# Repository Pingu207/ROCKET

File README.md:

# ROCKET (TVC)

A rocket using thrust vector control (TVC), with an onboard ESP32-WROOM-32 flight computer and sensors on a custom PCB.

## Overview
This project combines a gimbaled thrust-vectoring motor mount with a custom flight computer 
to actively stabilize the rocket during ascent. Progress is being logged as part of Hack 
Club's Stardance challenge.

## Hardware
- **MCU:** ESP32-WROOM-32
- **Barometer:** BMP280 (wired via I2C)
- **Servos:** 2x 20 kg·cm servos for TVC gimbal actuation
- **Power:** 2S LiPo battery for servo supply
- **Pyro channels:** Parachute ejection circuit (schematic complete)
- **PCB:** Custom board housing flight computer + sensors (schematic in progress)

## Mechanical
- TVC mount fully built, with weight-reduction holes machined in
- First servo mount CAD'd and finished
- Rocket body and nosecone modeled in CAD and assembled with the TVC assembly

## Flight Simulation
Simulated the rocket's altitude, velocity, and acceleration profile:
- Fit a polynomial thrust curve using regression (Desmos)
- Derived an ODE (Riccati equation) factoring in gravity and drag
- Solved numerically in Python (matplotlib) for performance
- **Result:** predicted apogee of 268.65 m at 7.66 seconds

## Project Status
- [x] TVC mount designed, built, and weight-optimized
- [x] Servo mount CAD finished
- [x] Body + nosecone CAD assembled with TVC
- [x] BMP280 wired (I2C)
- [x] Pyro firing (parachute ejection) circuit designed
- [x] Flight simulation (altitude/velocity/acceleration, apogee prediction)
- [x] Servo wiring for TVC actuation
- [x] GPS integration into schematic
- [x] Finish full PCB schematic
- [ ] PCB fabrication
- [ ] Static fire / ground testing  
- [ ] First test flight

## Devlog
Full build log with photos and hours logged: 
[Stardance project page](https://stardance.hackclub.com/projects/45265)

(The mount inside the rocket to hold the PCB on impact)

(An exploded CAD design of all the components inside the rocket)

(A fully CADded TVC mount with the mounting holes)

(The Front side of the 3d PCB CAD)

(This is the 2D model of the PCB with all of the components)

(This is the schematic of the PCB with everything routed)

(This is an image of the inside of the rocket and how its layout is)

(This is a photo of the rocket from the bottom)

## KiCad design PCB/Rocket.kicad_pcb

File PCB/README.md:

# Rocket Flight Computer

A custom flight computer for a TVC model rocket that steers the rocket during boost and deploys its parachutes on the way down.

## What it does
- **Steers the rocket** with thrust vector control: two servos gimbal the motor to keep the rocket flying straight.
- **Deploys recovery** with two pyro channels: a drogue chute at apogee and the main chute at a set altitude.
- **Logs the flight** (acceleration, rotation, altitude, servo positions, battery voltages) to a microSD card.

## How it works
An ESP32 reads an ICM-42688 IMU and a BMP280 barometer. It detects launch, tracks the rocket's orientation and drives the servos to correct any tilt. When the barometer shows the rocket has stopped climbing, it fires the drogue; the main fires lower on the way down. Each pyro channel is optoisolated by an optocoupler to protect the ESP32 and has continuity sensing, so the board confirms the e-matches are connected before launch.

The logic, servos and pyros each run from their own battery, so a servo stall or a pyro firing can't brown out the computer. The board is programmed over USB-C

## Computer Module Subsystem

Contains the ESP32 as the 'brain' of the board, contains decoupling/bulk capacitors for the ESP power pins, RC decoupling for sensing pins, 2 SPI and an I2C communication circuit, 2 switches for RESET/BOOT on the ESP, various other resistors for signal lines and pull up on I2C/SPI lines, and a buzzer for detection of the apparatus after landing.

## USB Input and Conversion(USB-UART) Subsystem

Uses a 14 pin USB-C Receptacle for programming of the ESP32 over USB(Note: On the PCB, only one side of the receptacle footprint is routed correctly due to space constraints, so it will only work when the cable is plugged in one specific way, not both). Contains a USBLC6-2SC6 transient voltage suppression diode array for ESD/Surge protection. The USB-UART conversion is handled by the CH340K, an auto reset transistor circuit is also in place to make the ESP32 enter boot mode when data is transferred. The VBUS from the USB can also power logic on the chip by feeding into the logic power buck converter(ORing with the battery), the line also contains a Schottky diode for protection.

## Barometer(BMP280) Subsystem

Uses the BMP280 as the barometer, contains 2 decoupling caps for the power pins and a pull up resistor for the SCL line. Wired for I2C communication with the ESP32. Since SDO is tied to GND and CSB is pulled high to +3V3, the BMP280 will be set to the I2C adress 0x76.

## Logic Power and GND subsystem

Uses a generic connector symbol(JST PH 2.0 connector is used on the PCB). Contains reverse protection and voltage testing(facilitated by ESP ADC pin(Sensor_VN or pin 5)) before the buck converter. The buck converter input is OR'd between the battery and the USBC VBUS input, so either can power the chip. The buck converter used is the AP63203WU, a 2A synchronous step-down (buck) DC-DC switching voltage regulator, which is used here to step down the voltage of the battery(2S LiPO, 7.4V nominal) to a usable 3.3V for the ESP32. It is fitted with its correct passives(Input and Output capacitors, inductors, and bootstrap capacitor) as specified by its datasheet(Note: No feedback resistors are required here because the chip outputs a fixed 3.3V due to its internal feedback loop). The output of the chip supplies power for all logic functions on the chip.

## SD Card Logging Subsystem

Uses an SD card slot for flight data logging. Wired SPI from the ESP32. Contains pullup resistors and proper decoupling/bulk caps.

## Servo Power Subsystem

Uses generic pin connectors here on the schematic and JST PH 2.0 on the PCB again. Uses an IRF7404 transistor for reverse protection. Power feeds into 2 TPS563200s, 3A step down voltage regulators. They have proper passives(Input and Output capacitors, inductors, bootstrap capacitor, and feedback resistor). They also have LEDs alongside each for indication. Power feeds into 2x3 pin headers where the servos will feed from, each power line contains a 470uF bulk cap. Each servo is also controlled via PWM from the ESP32.

## Pyro Firing Subsystem

Uses a generic connector symbol (JST PH 2.0 on the PCB). An SS34 Schottky diode provides reverse protection, and an LED shows when the pyro battery is connected. The battery voltage is measured by the ESP32. There are two firing channel(Drogue/Main). Each is driven by an ESP32 GPIO through a PC817 optocoupler. The optocoupler switches the gate of an IRLZ44N, with a 10k pulldown. The MOSFET switches the low side of the e-match, which connects to the board through 2-pin screw terminals. Each e-match has a flyback diode across it for protection. Each channel also has continuity sensing via an ESP32 ADC pin. The pyro ground is connected to the main GND through a 0Ω resistor. (Note: The continuity and voltage sensing need the grounds tied together. Also, the main channel uses an ESP strapping pin(IO5) so the pyro battery should only be connected once the board is powered on and on the pad.)
## Why I made it
I decided to design a PCB for this project in order to get experience with designing a more complex PCB with multiple subsystems, learn about embedded control, and fly a rocket without having to buy a COTS flight computer, because thats really cool you know?!!

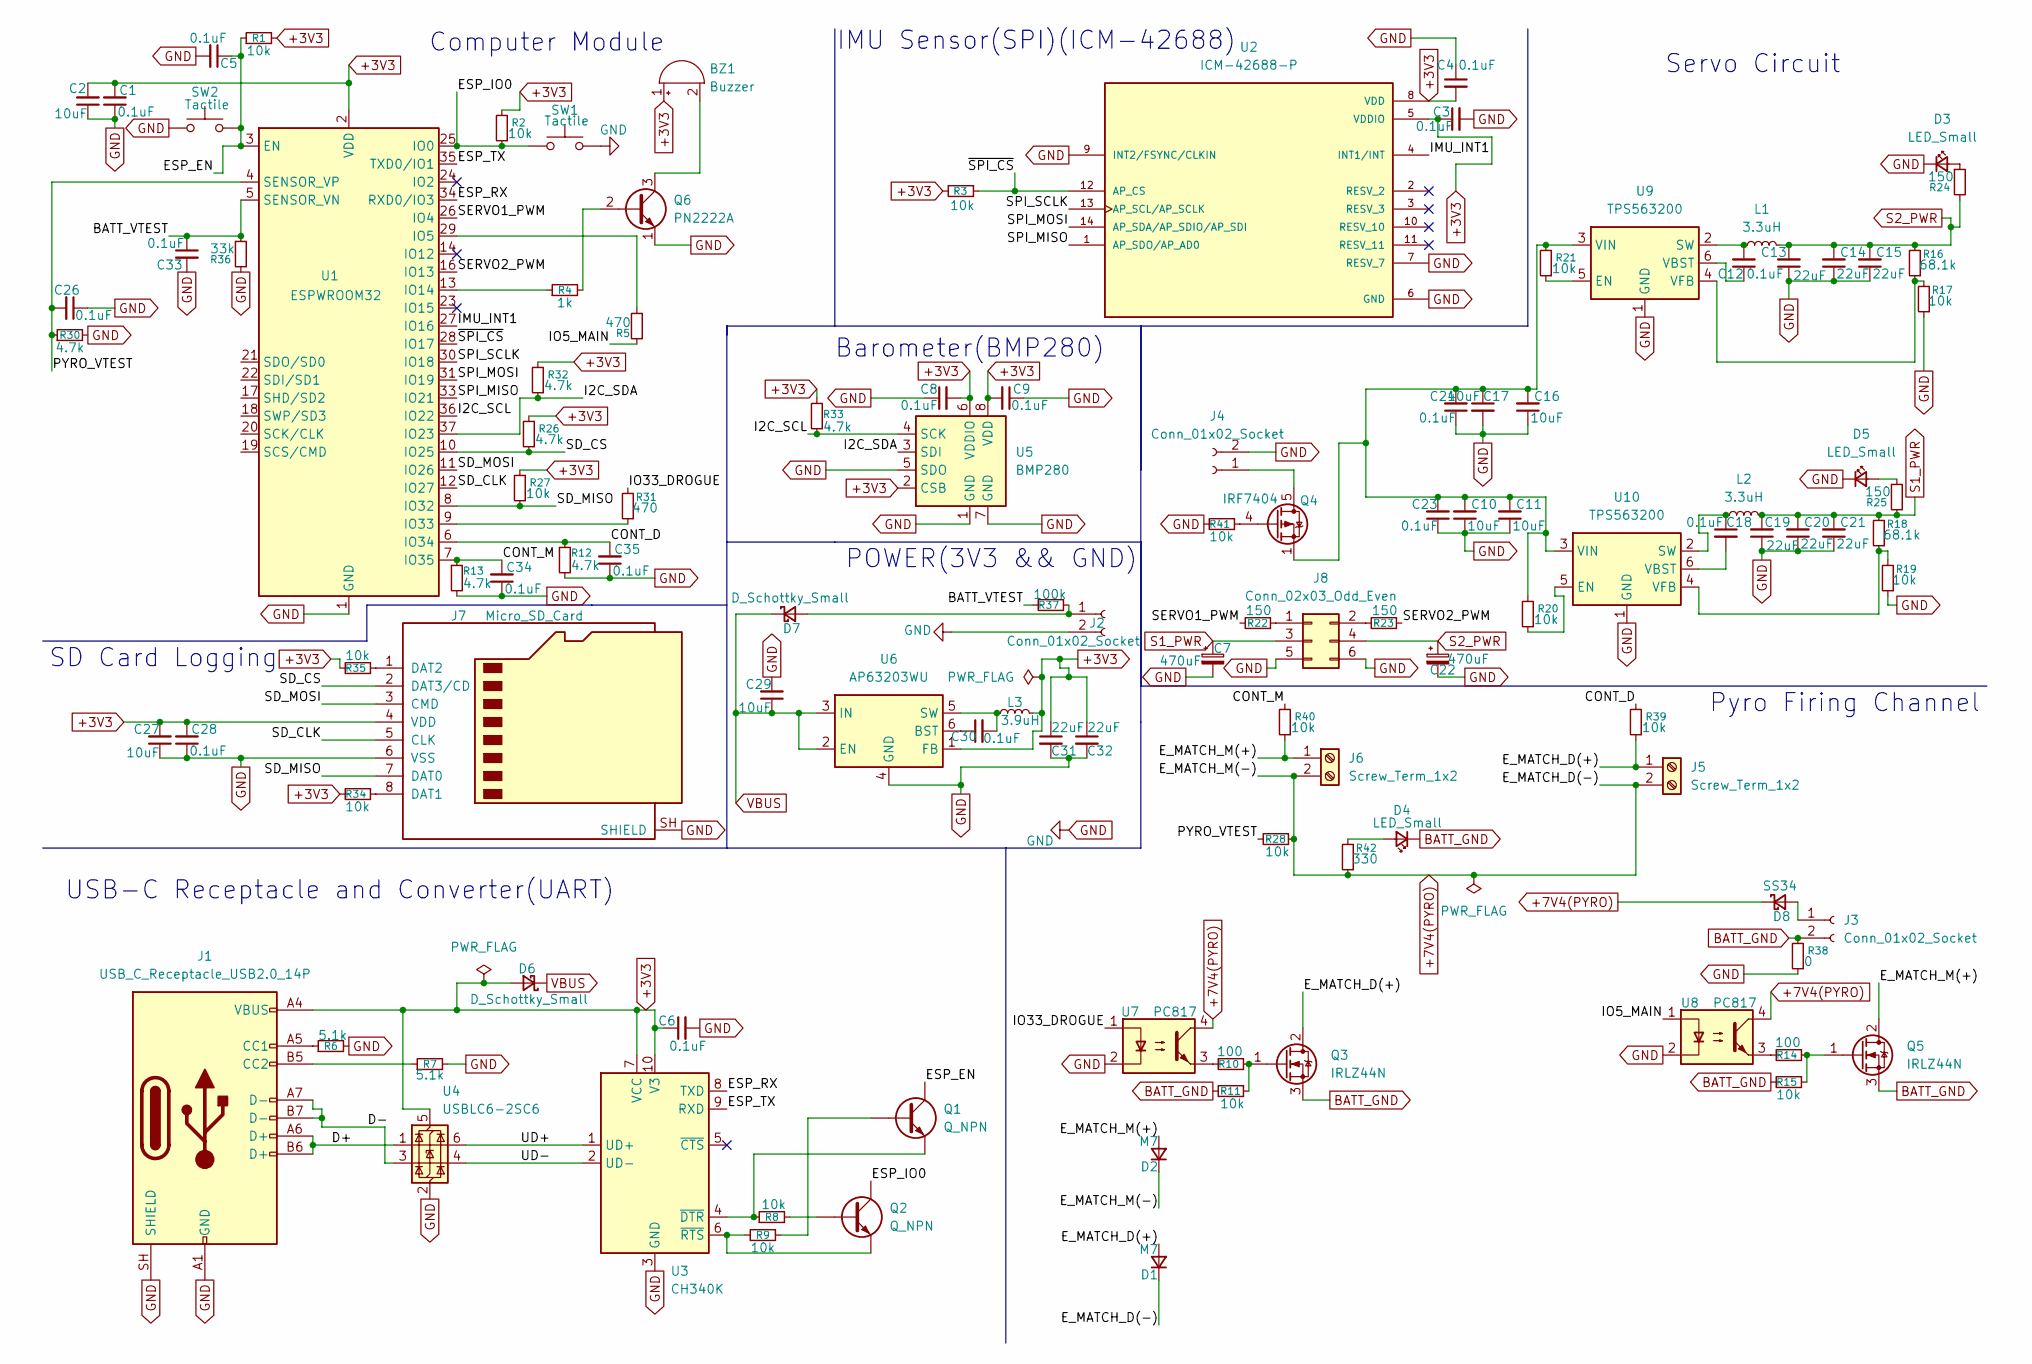
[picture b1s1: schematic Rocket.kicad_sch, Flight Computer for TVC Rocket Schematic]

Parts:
BZ1: Buzzer; BUZ-TH_BD9.0-P4.00-D0.6-FD; LCSC C96256
C1, C3, C4, C5, C6, C8, C9, C12, C18, C23, C24, C26, C28, C30, C33, C34, C35: 0.1uF; C0603; LCSC C125205
C2, C10, C11, C16, C17, C27, C29: 10uF; C0805; LCSC C440198
C7, C22: 470uF; CAP-SMD_BD10.0-L10.3-W10.3-FD; LCSC C976030
C13, C14, C15, C19, C20, C21, C31, C32: 22uF; C0805; LCSC C86816
D1, D2: M7; SMA_L4.3-W2.6-LS5.2-RD; LCSC C95872
D3, D4, D5: LED_Small; LED0603-FD; LCSC C19171390
D6, D7: D_Schottky_Small; SMC_L6.9-W5.9-LS7.9-RD; LCSC C154551
D8: SS34; SMC_L6.9-W5.9-LS7.9-RD; LCSC C154551
J1: USB_C_Receptacle_USB2.0_14P; USB-C-TH_KH-TYPE-C-CY-14P; LCSC C2919655
J2, J3, J4: Conn_01x02_Socket; CONN-TH_2P-P2.00_HC-PH-2A-M; LCSC C5359599
J5, J6: Screw_Term_1x2; CONN-TH_XY126V-5.0-2P; LCSC C557646
J7: Micro_SD_Card; TF-SMD_TF-115; LCSC C266620
J8: Conn_02x03_Odd_Even; HDR-TH_6P-P2.54-V-R2-C3-S2.54_A2541WV-2X3P; LCSC C5116479
L1, L2: 3.3uH; IND-SMD_L4.4-W4.2-A; LCSC C167207
L3: 3.9uH; IND-SMD_L5.0-W5.0; LCSC C42428060
Q1, Q2: Q_NPN; SOT-23-3_L3.0-W1.7-P0.95-LS2.9-BR; LCSC C2146
Q3, Q5: IRLZ44N; TO-220-3_L10.0-W4.5-P2.54-T; LCSC C38774
Q4: IRF7404; SOIC-8_L4.9-W3.9-P1.27-LS6.0-BL; LCSC C2997
Q6: PN2222A; TO-92-3_L4.9-W3.7-P1.27-L; LCSC C118536
R1, R2, R3, R8, R9, R11, R15, R17, R19, R20, R21, R27, R28, R34, R35, R39, R40, R41: 10k; R0603; LCSC C98220
R4: 1k; R0603; LCSC C22548
R5, R31: 470; R0603; LCSC C23179
R6, R7: 5.1k; R0603; LCSC C2907044
R10, R14: 100; R0603; LCSC C22775
R12, R13, R26, R30, R32, R33: 4.7k; R0603; LCSC C99782
R16, R18: 68.1k; R0603; LCSC C25976
R22, R23, R24, R25: 150; R0603; LCSC C2906994
R36: 33k; R0603; LCSC C2907028
R37: 100k; R0603; LCSC C14675
R38: 0; R0603; LCSC C95177
R42: 330; R0603; LCSC C105881
SW1, SW2: Tactile; SW-SMD_L3.9-W3.0-P4.45; LCSC C720477
U1: ESPWROOM32; WIFIM-SMD_ESP32-WROOM-32-N4; LCSC C82899
U2: ICM-42688-P; LGA-14_L3.0-W2.5-P0.50-TL; PARTREV 1.2; LCSC C1850418
U3: CH340K; ESOP-10_L4.9-W3.9-P1.00-LS6.2-BL-EP; LCSC C968586
U4: USBLC6-2SC6; SOT-23-6_L2.9-W1.6-P0.95-LS2.8-BL; LCSC C7519
U5: BMP280; LGA-8_L2.5-W2.0-P0.65_AMP6127; LCSC C83291
U6: AP63203WU; TSOT-26_L2.9-W1.6-P0.95-LS2.8-BL; LCSC C780769
U7, U8: PC817; DIP-4_L6.4-W4.6-P2.54-LS7.6-BL; LCSC C5350
U9, U10: TPS563200; TSOT-26_L2.9-W1.6-P0.95-LS2.8-BL; LCSC C97253

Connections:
+3V3: BZ1.1 (+), C1.2, C2.2, C3.1, C4.2, C6.1, C8.2, C9.2, C27.2, C28.2, C31.1, C32.1, D6.2 (A), J1.A4 (VBUS), J1.A9 (VBUS), J1.B4 (VBUS), J1.B9 (VBUS), J7.4 (VDD), L3.2, R1.2, R2.2, R3.2, R26.2, R27.2, R32.2, R33.2, R34.2, R35.2, U1.2 (VDD), U2.5 (VDDIO), U2.8 (VDD), U3.7 (VCC), U3.10 (V3), U4.5 (VBUS), U5.2 (CSB), U5.6 (VDDIO), U5.8 (VDD), U6.1 (FB)
+7V4(PYRO): D1.1 (K), D2.1 (K), D8.1 (K), J5.2, J6.2, R28.1, R42.1, U7.4, U8.4
/BATT_VTEST: C33.1, R36.1, R37.2, U1.5 (SENSOR_VN)
/CONT_D: C35.2, R12.1, R39.2, U1.6 (IO34)
/CONT_M: C34.2, R13.1, R40.2, U1.7 (IO35)
/D+: J1.A6 (D+), J1.B6 (D+), U4.1 (I/O1)
/D-: J1.A7 (D-), J1.B7 (D-), U4.3 (I/O2)
/ESP_EN: C5.1, Q1.3, R1.1, SW2.2, U1.3 (EN)
/ESP_IO0: Q2.3, R2.1, SW1.1, U1.25 (IO0)
/ESP_RX: U1.34 (RXD0/IO3), U3.8 (TXD)
/ESP_TX: U1.35 (TXD0/IO1), U3.9 (RXD)
/E_MATCH_D(+): D1.2 (A), J5.1, Q3.2 (D), R39.1
/E_MATCH_M(+): D2.2 (A), J6.1, Q5.2 (D), R40.1
/I2C_SCL: R33.1, U1.36 (IO22), U5.4 (SCK)
/I2C_SDA: R32.1, U1.37 (IO23), U5.3 (SDI)
/IMU_INT1: U1.27 (IO16), U2.4 (INT1/INT)
/IO5_MAIN: R5.1, U8.1
/IO33_DROGUE: R31.2, U7.1
/PYRO_VTEST: C26.2, R28.2, R30.1, U1.4 (SENSOR_VP)
/SD_CLK: J7.5 (CLK), U1.12 (IO27)
/SD_CS: J7.2 (DAT3/CD), R26.1, U1.10 (IO25)
/SD_MISO: J7.7 (DAT0), R27.1, U1.8 (IO32)
/SD_MOSI: J7.3 (CMD), U1.11 (IO26)
/SERVO1_PWM: R22.2, U1.26 (IO4)
/SERVO2_PWM: R23.1, U1.16 (IO13)
/SPI_MISO: U1.33 (IO21), U2.1 (AP_SDO/AP_AD0)
/SPI_MOSI: U1.31 (IO19), U2.14 (AP_SDA/AP_SDIO/AP_SDI)
/SPI_SCLK: U1.30 (IO18), U2.13 (AP_SCL/AP_SCLK)
/UD+: U3.1 (UD+), U4.6 (I/O1)
/UD-: U3.2 (UD-), U4.4 (I/O2)
/~SPI_CS: R3.1, U1.28 (IO17), U2.12 (AP_CS)
BATT_GND: D4.1 (K), J3.2, Q3.3 (S), Q5.3 (S), R11.2, R15.2, R38.2
GND: C1.1, C2.1, C3.2, C4.1, C5.2, C6.2, C7.2, C8.1, C9.1, C10.1, C11.1, C13.1, C14.1, C15.1, C16.1, C17.2, C19.1, C20.1, C21.1, C22.2, C23.1, C24.1, C26.1, C27.1, C28.1, C29.2, C31.2, C32.2, C33.2, C34.1, C35.1, D3.1 (K), D5.1 (K), J1.A1 (GND), J1.A12 (GND), J1.B1 (GND), J1.B12 (GND), J1.SH (SHIELD), J2.2, J4.2, J7.6 (VSS), J7.SH (SHIELD), J8.5, J8.6, Q6.1 (E), R6.2, R7.2, R12.2, R13.2, R17.1, R19.1, R30.2, R36.2, R38.1, R41.2, SW1.2, SW2.1, U1.1 (GND), U1.15 (GND), U1.38 (GND), U1.39 (GND), U2.6 (GND), U2.7 (RESV_7), U2.9 (INT2/FSYNC/CLKIN), U3.3 (GND), U3.11 (GND), U4.2 (GND), U5.1 (GND), U5.5 (SDO), U5.7 (GND), U6.4 (GND), U7.2, U8.2, U9.1 (GND), U10.1 (GND)
unnamed: BZ1.2 (-), Q6.3 (C)
unnamed: D3.2 (A), R24.1
unnamed: D4.2 (A), R42.2
unnamed: D5.2 (A), R25.1
unnamed: D7.2 (A), J2.1, R37.1
unnamed: D8.2 (A), J3.1
unnamed: J1.A5 (CC1), R6.1
unnamed: J1.B5 (CC2), R7.1
unnamed: J4.1, Q4.5 (D), Q4.6 (D), Q4.7 (D), Q4.8 (D)
unnamed: J7.8 (DAT1), R34.1
unnamed: J7.1 (DAT2), R35.1
unnamed: J8.1, R22.1
unnamed: J8.2, R23.2
unnamed: Q1.1, R9.1
unnamed: Q2.1, R8.2
unnamed: Q3.1 (G), R10.1, R11.1
unnamed: Q4.4 (G), R41.1
unnamed: Q5.1 (G), R14.1, R15.1
unnamed: Q6.2 (B), R4.2
unnamed: R10.2, U7.3
unnamed: R14.2, U8.3
unnamed: R5.2, U1.29 (IO5)
unnamed: R4.1, U1.13 (IO14)
unnamed: R31.1, U1.9 (IO33)
unnamed: Q1.2, R8.1, U3.4 (~DTR)
unnamed: Q2.2, R9.2, U3.6 (~RTS)
unnamed: C30.1, U6.6 (BST)
unnamed: C30.2, L3.1, U6.5 (SW)
unnamed: R21.1, U9.5 (EN)
unnamed: C12.2, L1.1, U9.2 (SW)
unnamed: C12.1, U9.6 (VBST)
unnamed: R16.1, R17.2, U9.4 (VFB)
unnamed: R20.1, U10.5 (EN)
unnamed: C18.1, L2.1, U10.2 (SW)
unnamed: C18.2, U10.6 (VBST)
unnamed: R18.1, R19.2, U10.4 (VFB)
unnamed: C10.2, C11.2, C16.2, C17.1, C23.2, C24.2, Q4.1 (S), Q4.2 (S), Q4.3 (S), R20.2, R21.2, U9.3 (VIN), U10.3 (VIN)
S1_PWR: C7.1, C19.2, C20.2, C21.2, J8.3, L2.2, R18.2, R25.2
S2_PWR: C13.2, C14.2, C15.2, C22.1, J8.4, L1.2, R16.2, R24.2
VBUS: C29.1, D6.1 (K), D7.1 (K), U6.2 (EN), U6.3 (IN)

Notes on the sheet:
IMU Sensor(SPI)(ICM-42688)
SD Card Logging
Servo Circuit
Computer Module
Pyro Firing Channel
USB-C Receptacle and Converter(UART)
Barometer(BMP280)
POWER(3V3 && GND)

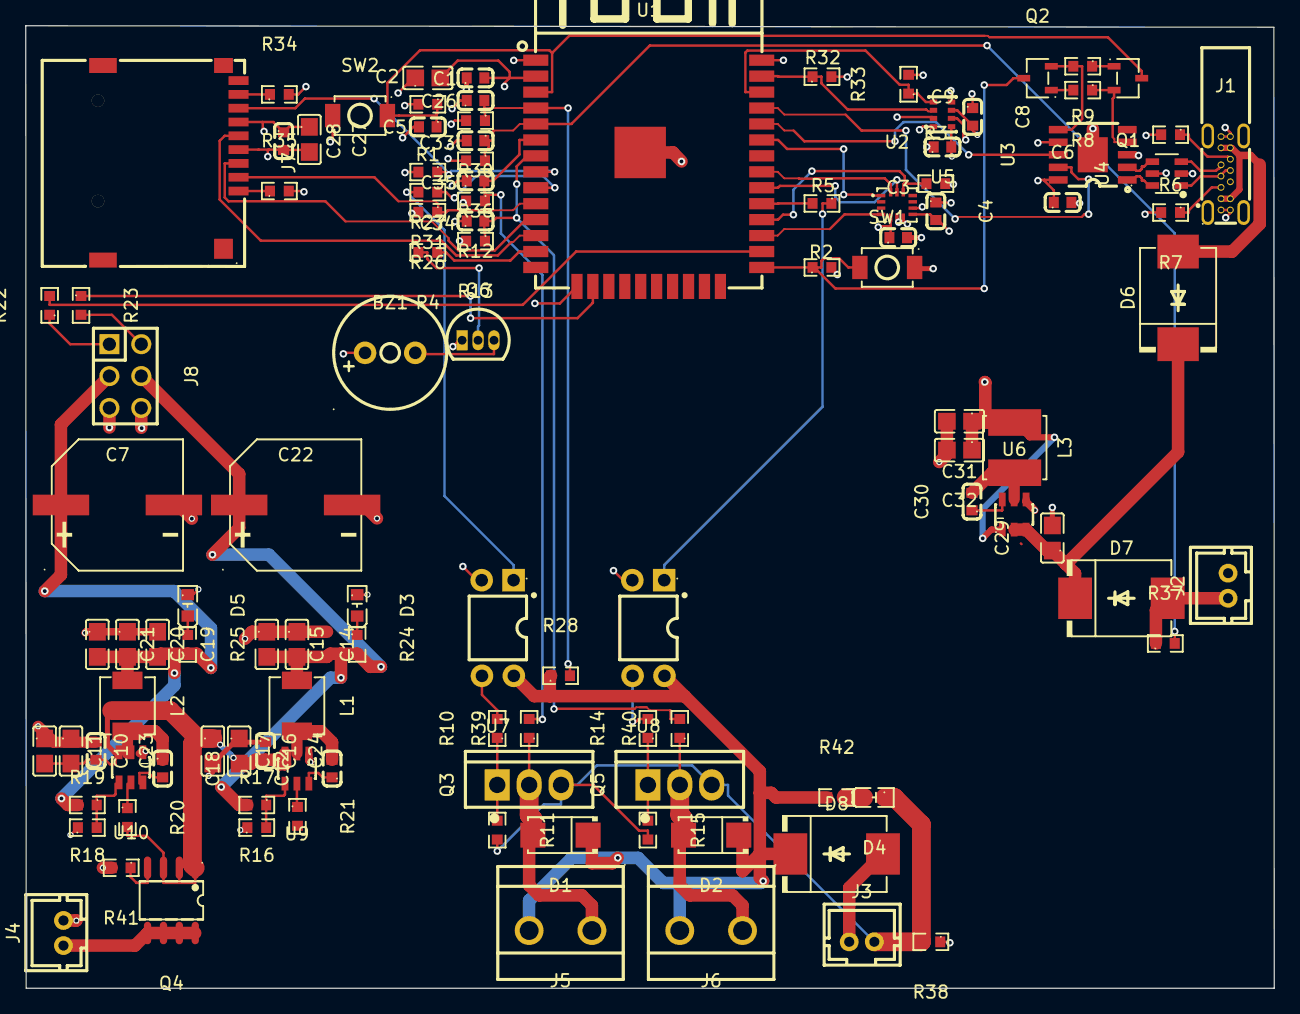
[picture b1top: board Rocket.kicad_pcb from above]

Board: 4 copper layers, 99.5 x 76.7 mm, 112 parts (0 on the bottom side), 73 nets.

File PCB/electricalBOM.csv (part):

JLCPCB BOM Tool - BOM Matching,,,,,,,,,,,,,,,,
BOM name：bom-JLCPCB Assembly Order.xlsx,,,Download Time：2026-10-25 23:32:35,,,,"* Our matching results are updated in real-time, but stock and prices may change. 
 If it's been over 24 hours, please re-match before placing your order.",,,,,,,,,
PCB Assembled Qty：5,,,Est. Total Price：278.1183,,,,,,,,,,,,,
Your BOM,,,,Matched Parts,,,,,,,Order Information,,,,,
Designator,Comment,Footprint,JLCPCB Part #,Matches,Part #,Manufacturer,Footprint,Description,Category,Warning,JLCPCB Part #,Product link,Lib Type,Qty,Source,Total Price ($)
BZ1,Buzzer,BUZ-TH_BD9.0-P4.00-D0.6-FD,,Select by System,QMB-09B-03,Jiangsu Huaneng Elec,"插件,D=9mm","-20℃~+70℃ 2.7kHz 2V~5V 3V 5.7mm 50mA 85dB 9mm Electromagnetic Passive (Externally Driven) 插件,D=9mm Buzzers ROHS",Buzzers,,C96256,https://jlcpcb.com/partdetail/Jiangsu_HuanengElec-QMB_09B03/C96256,Extended,6,6 JLCPCB,0.708
"C1,C12,C18,C23,C24,C26,C28,C3,C30,C33,C34,C35,C4,C5,C6,C8,C9",0.1uF,C0603,,Select by System,CT41G-0603-2X1-50V-0.1uF-K(N),TORCH,603,100nF 50V ±10% 0603 Multilayer Ceramic Capacitors MLCC - SMD/SMT ROHS,Multilayer Ceramic Capacitors MLCC - SMD/SMT,,C125205,https://jlcpcb.com/partdetail/TORCH-CT41G_0603_2X1_50V_0_1uF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,Extended,91,91 JLCPCB,0.9919
"C10,C11,C16,C17,C2,C27,C29",10uF,C0805,,Select by System,GRM21BR61H106KE43L,Murata Electronics,805,10uF 50V X5R ±10% 0805 Multilayer Ceramic Capacitors MLCC - SMD/SMT ROHS,Multilayer Ceramic Capacitors MLCC - SMD/SMT,,C440198,https://jlcpcb.com/partdetail/439567-GRM21BR61H106KE43L/C440198,Basic,37,37 JLCPCB,7.6923
"C13,C14,C15,C19,C20,C21,C31,C32",22uF,C0805,,Select by System,GRM21BR61E226ME44L,Murata Electronics,805,22uF 25V X5R ±20% 0805 Multilayer Ceramic Capacitors MLCC - SMD/SMT ROHS,Multilayer Ceramic Capacitors MLCC - SMD/SMT,,C86816,https://jlcpcb.com/partdetail/MurataElectronics-GRM21BR61E22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,Extended,44,44 JLCPCB,10.5644
"C22,C7",470uF,CAP-SMD_BD10.0-L10.3-W10.3-FD,,Select by System,RVT1V471M1010 470UF 35V,DMBJ,"SMD,D10xL10.2mm","-55℃~+105℃ 10.2mm 10mm 2800hrs@105℃ 35V 470uF ±20% SMD,D10xL10.2mm Aluminum Electrolytic Capacitors - SMD ROHS",Aluminum Electrolytic Capacitors - SMD,,C976030,https://jlcpcb.com/partdetail/DMBJ-RVT1V471M1010_470UF35V/C976030,Extended,10,10 JLCPCB,0.909
"D1,D2",M7,SMA_L4.3-W2.6-LS5.2-RD,,Select by System,M7,MDD(Microdiode Semiconductor),SMA(DO-214AC),-55℃~+150℃ 1.1V@1A 1A 1kV 30A 5uA@1kV Independent SMA(DO-214AC) Diodes - General Purpose ROHS,Diodes - General Purpose,,C95872,https://jlcpcb.com/partdetail/MDD_Microdiode_Semiconductor-M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,Basic,20,20 JLCPCB,0.206
"D3,D4,D5",LED_Small,LED0603-FD,,Select by System,YLED0603R,YONGYUTAI,603,-40℃~+85℃ 1.8V~2.4V 120mcd 120° 25mA 620nm~625nm Discrete Diode Red 0603 LED Indication - Discrete ROHS,LED Indication - Discrete,,C19171390,https://jlcpcb.com/partdetail/YONGYUTAI-YLED0603R/C19171390,Extended,31,31 JLCPCB,0.1953
"D6,D7",D_Schottky_Small,SMC_L6.9-W5.9-LS7.9-RD,,Unconfirmed,SS34,onsemi,SMC(DO-214AB),-55℃~+150℃ 1 Independent 100A 3A 40V 500mV@3A 500uA@40V SMC(DO-214AB) Schottky Diodes ROHS,Schottky Diodes,1.Multiple lines in the BOM have been matched to the same part. Please check if the matching is correct. ;,C154551,https://jlcpcb.com/partdetail/onsemi-SS34/C154551,Extended,15,15 JLCPCB,7.1445
D8,SS34,SMC_L6.9-W5.9-LS7.9-RD,,Unconfirmed,,,,,,,,,,,,
J1,USB_C_Receptacle_USB2.0_14P,USB-C-TH_KH-TYPE-C-CY-14P,,Select by System,KH-TYPE-C-CY-14P,Shenzhen Kinghelm Elec,插件,"-40℃~+85℃ 1 10,000 cycles 14P 14mm 20V 3A Black Female Type-C Vertical, Flag 插件 USB Connectors ROHS",USB Connectors,,C2919655,https://jlcpcb.com/partdetail/3222637-KH_TYPE_C_CY14P/C2919655,Extended,5,5 JLCPCB,2.7575
"J2,J3,J4",Conn_01x02_Socket,CONN-TH_2P-P2.00_HC-PH-2A-M,,Select by System,WAFER-PH2.0-2PZZ,XUNPU,"插件,P=2mm","-25℃~+85℃ 1 1x2P 2 250V 2A 2P 2mm 4.7mm 6.05mm 6mm Brass PA66 PH Through Hole Tin UL94V-0 White 插件,P=2mm Wire To Board Connector ROHS",Wire To Board Connector,,C5359599,https://jlcpcb.com/partdetail/XUNPU-WAFER_PH2_02PZZ/C5359599,Extended,20,20 JLCPCB,0.278
"J5,J6",Screw_Term_1x2,CONN-TH_XY126V-5.0-2P,,Select by System,XY126V-5.0-2P,Ningbo Xinlaiya Elec.,"插件,P=5mm","1 10A 14~26 1x2P 2 2.5 2P 300V 5mm Green M2.5 Through Hole 插件,P=5mm Screw Terminal Blocks ROHS",Screw Terminal Blocks,,C557646,https://jlcpcb.com/partdetail/Ningbo_Xinlaiya_Elec-XY126V_5_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,Extended,11,11 JLCPCB,1.0659
J7,Micro_SD_Card,TF-SMD_TF-115,,Select by System,TF-115,XUNPU,SMD,1.8mm Connector and Ejector MicroSD Card (TF Card) Push-Push SMD SD Card / Memory Card Connector ROHS,SD Card / Memory Card Connector,,C266620,https://jlcpcb.com/partdetail/XUNPU-TF115/C266620,Extended,6,6 JLCPCB,1.0452
J8,Conn_02x03_Odd_Even,HDR-TH_6P-P2.54-V-R2-C3-S2.54_A2541WV-2X3P,,Select by System,2.54-2*3,ZHOURI,"插件,P=2.54mm","-40℃~+105℃ 2 2.54mm 2.54mm 2.54mm 2.5A 2x3P 3mm 6P 6mm Brass Gold Pin Header Through Hole 插件,P=2.54mm Pin Headers ROHS",Pin Headers,,C5116479,https://jlcpcb.com/partdetail/ZHOURI-2_54_23/C5116479,Extended,5,5 JLCPCB,0.2995
"L1,L2",3.3uH,IND-SMD_L4.4-W4.2-A,,Select by System,FXL0420-3R3-M,cjiang (Changjiang Microelectronics Tech),"SMD,4.4x4.2mm","3.3A 3.3uH 4A 87mΩ Molded inductor ±20% SMD,4.4x4.2mm Molding Power Inductors ROHS",Power Inductors,,C167207,https://jlcpcb.com/partdetail/178590-FXL0420_3R3M/C167207,Extended,12,12 JLCPCB,1.6896
L3,3.9uH,IND-SMD_L5.0-W5.0,,Select by System,ZENR5040T3R9N-3.9uH,ZE,"SMD,5x5mm","27mΩ 3.2A 3.55A 3.9uH Magnetic Shielded Inductor ±30% SMD,5x5mm Power Inductors ROHS",,,C42428060,https://jlcpcb.com/partdetail/ZE-ZENR5040T3R9N_39uH/C42428060,Extended,7,7 JLCPCB,0.4424
"Q1,Q2",Q_NPN,SOT-23-3_L3.0-W1.7-P0.95-LS2.9-BR,,Select by System,S8050 J3Y(RANGE:200-350),"Jiangsu Changjing Electronics Technology Co., Ltd.",SOT-23,-55℃~+150℃ 1 NPN 100nA 150MHz 200 25V 300mW 500mA 5V 600mV NPN SOT-23 Bipolar (BJT) ROHS,Bipolar (BJT),,C2146,https://jlcpcb.com/partdetail/2503-S8050_J3Y_RANGE_200_350/C2146,Basic,15,15 JLCPCB,0.213
"Q3,Q5",IRLZ44N,TO-220-3_L10.0-W4.5-P2.54-T,,Select by System,IRLZ44NPBF,Infineon Technologies,TO-220AB,-55℃~+175℃ 1 N-channel 1.7nF 110W 150pF 25mΩ@5V 2V 400pF 47A 48nC@5V 55V N-Channel TO-220AB MOSFETs ROHS,MOSFETs,,C38774,https://jlcpcb.com/partdetail/InfineonTechnologies-IRLZ44NPB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,Extended,10,10 JLCPCB,7.185
Q4,IRF7404,SOIC-8_L4.9-W3.9-P1.27-LS6.0-BL,,Select by System,IRF7404TRPBF,Infineon Technologies,SO-8,-55℃~+150℃ 1 P-Channel 1.5nF 2.5W 20V 340pF 40mΩ@4.5V 50nC@4.5V 6.7A 700mV 730pF P-Channel SO-8 MOSFETs ROHS,MOSFETs,,C2997,https://jlcpcb.com/partdetail/InfineonTechnologies-IRF7404TR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,Extended,5,5 JLCPCB,10.1055
Q6,PN2222A,TO-92-3_L4.9-W3.7-P1.27-L,,Select by System,2N2222A,ST(Semtech),TO-92,1 NPN 10nA 1V 250MHz 40 40V 600mA 625mW 6V NPN TO-92 Bipolar (BJT) ROHS,Bipolar (BJT),,C118536,https://jlcpcb.com/partdetail/ST_Semtech-2N2222A/C118536,Extended,8,8 JLCPCB,0.312
"R1,R11,R15,R17,R19,R2,R20,R21,R27,R28,R3,R34,R35,R39,R40,R41,R8,R9",10k,R0603,,Select by System,RC0603FR-0710KL,YAGEO,603,-55℃~+155℃ 100mW 10kΩ 75V Thick Film Resistor ±1% ±100ppm/℃ 0603 Chip Resistor - Surface Mount ROHS,Chip Resistor - Surface Mount,,C98220,https://jlcpcb.com/partdetail/YAGEO-RC0603FR0710KL/C98220,Extended,100,100 JLCPCB,0.27
R4,1k,R0603,,Select by System,RC0603FR-071KL,YAGEO,603,-55℃~+155℃ 100mW 1kΩ 75V Thick Film Resistor ±1% ±100ppm/℃ 0603 Chip Resistor - Surface Mount ROHS,Chip Resistor - Surface Mount,,C22548,https://jlcpcb.com/partdetail/YAGEO-RC0603FR071KL/C22548,Extended,20,20 JLCPCB,0.072
"R6,R7",5.1k,R0603,,Select by System,FRC0603F5101TS,FOJAN,603,-55℃~+155℃ 100mW 5.1kΩ 75V Thick Film Resistor ±1% ±100ppm/℃ 0603 Chip Resistor - Surface Mount ROHS,Chip Resistor - Surface Mount,,C2907044,https://jlcpcb.com/partdetail/FOJAN-FRC0603F5101TS/C2907044,Extended,20,20 JLCPCB,0.038
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
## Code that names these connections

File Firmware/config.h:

#pragma once
/*
 * Rocket flight computer - board configuration
 * Pin map taken from the Rocket.kicad_sch netlist (ESP32-WROOM-32).
 */
#include "esp_adc/adc_oneshot.h"

/* ---------------- Pins ---------------- */
/* ICM-42688-P IMU, SPI (SPI2_HOST) */
#define PIN_IMU_CS        17
#define PIN_IMU_SCLK      18
#define PIN_IMU_MOSI      19
#define PIN_IMU_MISO      21
#define PIN_IMU_INT1      16   /* wired, not used: IMU is polled */

/* BMP280 barometer, I2C (SDO->GND => addr 0x76, CSB->3V3 => I2C mode) */
#define PIN_I2C_SDA       23
#define PIN_I2C_SCL       22
#define BMP280_ADDR       0x76

/* microSD, SPI (SPI3_HOST) */
#define PIN_SD_CLK        27
#define PIN_SD_MOSI       26
#define PIN_SD_MISO       32
#define PIN_SD_CS         25

/* Pyro channels: GPIO HIGH -> optocoupler LED on -> MOSFET fires */
#define PIN_PYRO_DROGUE   33
#define PIN_PYRO_MAIN      5   /* WARNING: IO5 is a strapping pin, see README */

/* TVC servos (LEDC PWM) */
#define PIN_SERVO_PITCH    4   /* J8 pin 1, SERVO1_PWM */
#define PIN_SERVO_YAW     13   /* J8 pin 2, SERVO2_PWM */

/* Buzzer via Q6 */
#define PIN_BUZZER        14
#define BUZZER_FREQ_HZ  2700   /* works for passive; active buzzers also sound */

/* ADC1 channels (ADC1 keeps working with WiFi on) */
#define ADC_CH_PYRO_VTEST ADC_CHANNEL_0  /* IO36 */
#define ADC_CH_BATT_VTEST ADC_CHANNEL_3  /* IO39 */
#define ADC_CH_CONT_D     ADC_CHANNEL_6  /* IO34 */
#define ADC_CH_CONT_M     ADC_CHANNEL_7  /* IO35 */

/* Divider ratios (Vadc = Vin * ratio), values read from the schematic */
#define DIV_PYRO   (4.7f / (10.0f + 4.7f))    /* R28 10k / R30 4.7k */
#define DIV_CONT   (4.7f / (10.0f + 4.7f))    /* R39/R12, R40/R13   */
#define DIV_BATT   (33.0f / (100.0f + 33.0f)) /* R37 100k / R36 33k */

/* ---------------- Timing ---------------- */
#define CONTROL_HZ          200     /* IMU + TVC loop */
#define BARO_DIV              4     /* baro every 4th loop  -> 50 Hz */
#define ADC_DIV              20     /* ADC every 20th loop  -> 10 Hz */
#define LOG_DIV               2     /* log every 2nd loop   -> 100 Hz */

/* ---------------- Flight logic ---------------- */
#define LAUNCH_ACCEL_G       3.0f   /* |a| above this ...            */
#define LAUNCH_ACCEL_MS        50   /* ... for this long = launch    */
#define LAUNCH_ALT_M        20.0f   /* or baro climbs this much      */
#define BURNOUT_ACCEL_G      0.5f   /* axial accel below this ...    */
#define BURNOUT_MS            100   /* ... for this long = burnout   */
#define MAX_BURN_MS          8000   /* force COAST after this        */
#define APOGEE_LOCKOUT_MS    4000   /* no apogee before this (transonic baro spikes) */
#define APOGEE_CONFIRM          5   /* consecutive baro samples with v < 0 */
#define MAIN_DEPLOY_ALT_M  150.0f   /* main fires below this AGL on descent */
#define PYRO_PULSE_MS        1000   /* firing pulse length */
#define PYRO_MIN_V           6.0f   /* warn if pyro battery below this */
#define CONT_THRESH_FRAC     0.5f   /* CONT > frac * Vpyro => e-match present */
#define LANDED_SPEED_MS      1.0f
#define LANDED_HOLD_MS       5000

/* Baro alpha-beta filter */
#define AB_ALPHA             0.20f
#define AB_BETA              0.02f

/* ---------------- TVC ---------------- */
/* Gains: gimbal degrees per degree of tilt error. MUST be tuned for your airframe. */
#define TVC_KP               0.60f
#define TVC_KI               0.10f
#define TVC_KD               0.15f  /* per deg/s of body rate */
#define TVC_I_LIMIT          3.0f   /* integral clamp, gimbal deg */
#define TVC_MAX_DEG          5.0f   /* mechanical gimbal limit */

#define SERVO_CENTER_US      1500
#define SERVO_US_PER_DEG     10.0f  /* depends on linkage - CALIBRATE */
#define SERVO_PITCH_SIGN     (+1)   /* flip if servo corrects the wrong way */
#define SERVO_YAW_SIGN       (+1)
#define SERVO_PITCH_TRIM_US  0
#define SERVO_YAW_TRIM_US    0

/*
 * IMU axis mapping. Body frame: +Z = rocket nose, X/Y = gimbal axes.
 * Body axis n = SIGN_n * sensor axis IDX_n.  Verify with the pad telemetry:
 * standing the rocket upright must give az ~ +1 g and tilt ~ 0.
 */
#define BODY_X_IDX  0
#define BODY_X_SIGN (+1)
#define BODY_Y_IDX  1
#define BODY_Y_SIGN (+1)
#define BODY_Z_IDX  2
#define BODY_Z_SIGN (+1)
